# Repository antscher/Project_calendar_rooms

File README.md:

# Room Calendar Management System

## Project Overview
The Room Calendar Management System is a modern solution for managing meeting room availability using IoT devices. The system combines hardware displays mounted outside each room with a centralized software management platform.

## Project Goals
- Eliminate double-bookings and confusion around room availability
- Provide real-time room status information
- Reduce energy consumption with e-ink displays
- Enable easy room booking directly from the display (by Qr code) or web interface
- Integrate with existing calendar systems

## System Architecture

### Hardware Components
1. **Room Displays**
   - ESP32-S2 microcontroller
   - Waveshare E-ink display
   - Non - Rechargeable battery system
   - QR code for booking

2. **Server Infrastructure**
   - Central management server
   - WiFi network integration

### Software Components
1. **Backend System**
   - Room management
   - Booking system
   - User authentication
   - Calendar integration

2. **Frontend Interfaces**
   - Web dashboard for administrators
   - Display interface for e-ink screens

## Key Features
- Real-time room availability display
- Direct booking from room displays
- Low-power operation with years of battery life
- Calendar synchronization
- Administrative dashboard

## System Illustrations

### Example Screens and Interfaces

#### Calendar Example

#### Reserved Calendar Example

#### On Air Screen

#### Mosquitto Server Control

## Expected Benefits
- Improved room utilization
- Reduced booking conflicts
- Enhanced user experience
- Energy-efficient operation

## Project Structure
```
Project_calendar_rooms/
├── code_esp32/                      # ESP32 firmware and related tools
|   ├── font2bytes-dynamics/         # Tool for converting fonts to byte arrays
│   └── main/                        # Main ESP32 application code
├── Hardware/                        # Hardware design files
│   ├── cadre room V_.svg/           # Display frame design (version _)
│   ├── Support cadre V_.stl/        # Support of the cadre to be print in 3d (version _)
│   └── esp32 room pcb/              # Custom PCB design for ESP32
└── code_service_server_python/      # Server-side Python applications
    ├── mqtt_service/                # MQTT broker and message handling service
    └── web_local_consol/            # Local web console for room management
```

## License
This project is licensed under GNU GENERAL PUBLIC LICENSE V3 - see the LICENSE.md file for details.

## Main Contributor
This project was developed by Antoine Scherpereel as part of an intership project at ISU (International Space University).

For questions or support, contact:
- Antoine Scherpereel
- Email: antoine.scherpereel@isunet.edu

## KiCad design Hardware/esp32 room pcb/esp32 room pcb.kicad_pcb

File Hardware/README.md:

# Hardware Components Selection

## ESP32-S2 Microcontroller : ESP32-S2 pico from waveshare
Here the link : https://www.waveshare.com/esp32-s2.htm
- **Why this choice?**
  - Built-in WiFi capabilities for network connectivity
  - Low power consumption with deep sleep modes
  - Sufficient GPIO pins for e-ink display interface
  - Cost-effective solution for IoT applications
  - Native USB support for easy programming
  - Enough RAM for rendering the image before displaying it

  Can be power supply between 10V and 1.8V theorically in reality it is needed to be superior to 2.65V

## Waveshare E-Ink Display : Spectra 7.3" from Waveshare
Here the link : https://www.waveshare.com/7.3inch-e-paper-hat-e.htm 
- **Why this choice?**
  - Ultra-low power consumption - only uses power when refreshing
  - Excellent readability in various lighting conditions
  - Maintains display without power
  - Available SPI interface for easy integration with ESP32
  - 6 colors 

## Battery Selection : Roomz display battery
Here the link : https://www.bechtle.com/fr-en/shop/roomz-display-spare-batteries--4329865--p
- **Why not rechargeable Li-primary**
  - High energy density
  - Low self-discharge rate
  - Long cycle life
  - Safe for fire problems

  Normally the battery will stay really close to 3V during all it live cycle but a varation can cause effects.
  Capacity (%)	Voltage (V)
  100%	        3.0 – 3.2 V
  90%	          3.0 – 3.1 V
  80%	          2.95 – 3.1 V
  50%	          2.9 – 3.0 V
  20%	          2.8 – 2.9 V
  10%	          2.7 – 2.8 V
  0%          	~2.0 – 2.5 V

  Note : After testing with different input voltage, the results are : 
  - > 2.65V : work normally
  - between 2.65 and 2.4 : work but risk of losing is SPRAM
  - < 2.4 V : not working at all

  Conclusion : we can use even if we consider there is risk of malfounctionning at the end of life
  (Possibility utilising NVS memory but there is a limit in R/W cycle)

## Power Considerations
- E-ink display only draws power during updates
- ESP32-S2 deep sleep mode < 10µA
- Expected battery life: 2-3 years between replacing battery

## The PCB 

The pcb is made on Kicad
You can open it and modify it with Kicad, may be you will need to downloads some library for footprints
You can purshase it, but you have to first expot in gerber file.
All of the componnent required are in the "Component list.xlsx", you can change some component by similar ones but make sure the footprint is compatible (or modify it).

## The support of the frame

It is made in Fusion 360, you have access to the STL file to print the design.
Use M3 screws to attach it.

## The frame

The frame is made with Inkscape, it is a .svg file.
It is designed for 3mm wood.
It needs to be cut (red lines) and engraved (blue surface).
You need to glue it except the back, which just fits in so you can remove it after.
For the screen, tape it or glue it.

### Frame Images

See the following images for reference:
- 
-

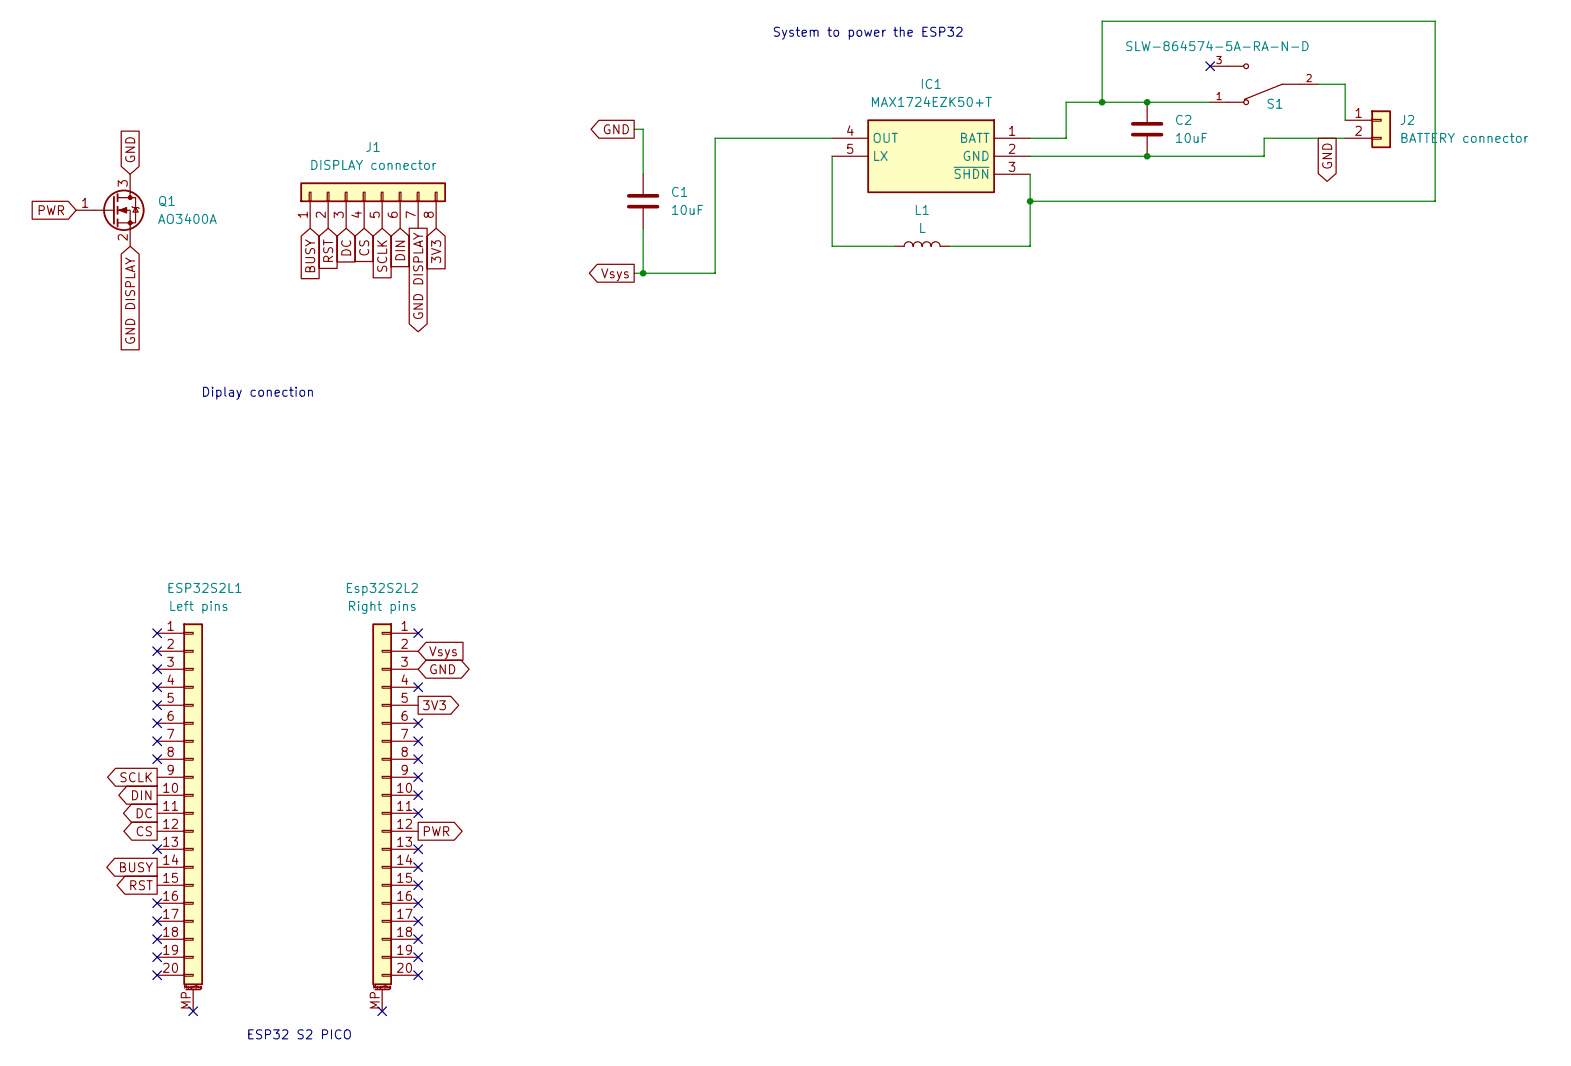
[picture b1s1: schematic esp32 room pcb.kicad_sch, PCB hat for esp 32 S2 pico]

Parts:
C1, C2: 10uF; C_0805_2012Metric
ESP32S2L1: Left pins; PinSocket_1x20_P2.54mm_Vertical
Esp32S2L2: Right pins; PinSocket_1x20_P2.54mm_Vertical
IC1: MAX1724EZK50+T; SOT95P275X110-5N; Mouser Part Number 700-MAX1724EZK50T
J1: DISPLAY connector; PinHeader_1x08_P2.54mm_Horizontal
J2: BATTERY connector; JST_PH_S2B-PH-SM4-TB_1x02-1MP_P2.00mm_Horizontal
L1: L; SRR1260100M
Q1: AO3400A; SOT-23
S1: SLW-864574-5A-RA-N-D; SW_SLW-864574-5A-RA-N-D; PARTREV 1.01

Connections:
3V3: Esp32S2L2.5, J1.8
BUSY: ESP32S2L1.14, J1.1
CS: ESP32S2L1.12, J1.4
DC: ESP32S2L1.11, J1.3
DIN: ESP32S2L1.10, J1.6
GND: C1.1, C2.2, Esp32S2L2.3, IC1.2 (GND), J2.2, Q1.3 (D)
GND DISPLAY: J1.7, Q1.2 (S)
unnamed: C2.1, IC1.1 (BATT), IC1.3 (~SHDN), L1.2, S1.1
unnamed: IC1.5 (LX), L1.1
unnamed: J2.1, S1.2
PWR: Esp32S2L2.12, Q1.1 (G)
RST: ESP32S2L1.15, J1.2
SCLK: ESP32S2L1.9, J1.5
Vsys: C1.2, Esp32S2L2.2, IC1.4 (OUT)

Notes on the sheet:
System to power the ESP32
Diplay conection
ESP32 S2 PICO

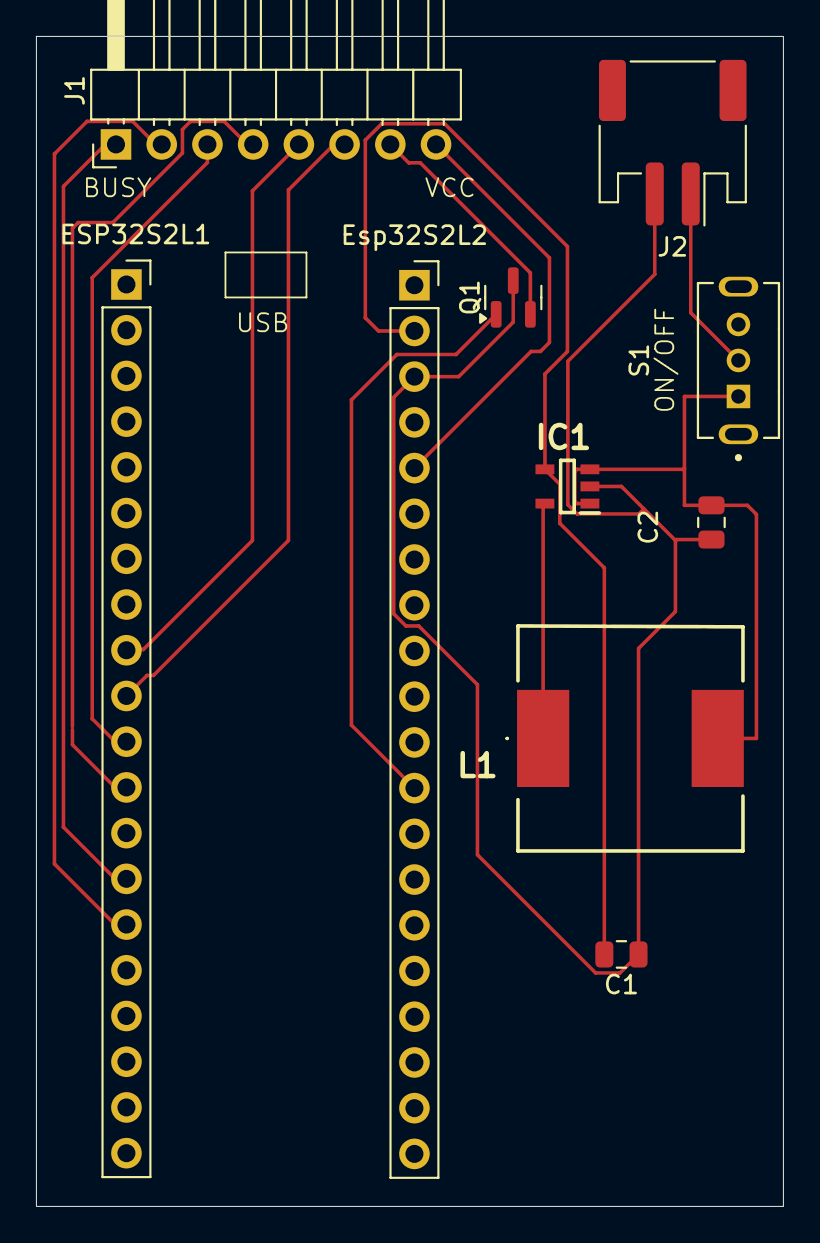
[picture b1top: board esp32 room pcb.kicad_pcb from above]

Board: 2 copper layers, 41.5 x 65.0 mm, 10 parts (0 on the bottom side), 14 nets.

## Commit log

2025-06-19 add README for hardwarw
2025-06-19 Add general presentation in README
2025-06-19 add of a readme for main
2025-06-19 update of the main README
2025-06-20 modification of foot print for battery connector
2025-06-24 ajout des tros pour le cadre
2025-06-24 correction diametre trous
2025-06-26 modification of the switch to a cheaper on
2025-06-26 modification du Readme de hardware
2025-07-01 corection et modification des bugs du à la basse tension (PCB + Arduino)
2025-07-02 correction des bugs de mises à jour et update du Readme
2025-07-02 modification design cadre
2025-07-02 add of the stl for support
2025-07-16 modification of the RTC Memory
2025-07-16 ajout memoire NVS pour room name
2025-07-16 modification of README
2025-07-16 traduction du site en anglais
2025-07-16 add of images
2025-07-16 changement position images
2025-07-17 ajout optimization memoire
2025-07-17 version beore merge
2025-07-17 new interface
2025-07-17 add image
2025-07-21 ajout d'un booster 5V pcb
2025-07-21 some modification flash frequency
2025-07-21 some description for part
2025-07-21 some description modification
2025-07-28 modify time
2025-07-28 add images
2025-07-28 modify hardware readme
2025-07-28 little change
